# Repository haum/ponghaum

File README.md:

# PongHaum

## Qu'est-ce que c'est ?

Ce dépôt contient les sources de ponghaum, le pong 1D réalisé par le HAUM (http://haum.org/)

## Arduino

### Présentation

Le système utilise 150 leds en bande commandées par la bibliothèque FastLED et deux boutons. Les détails du système est/sera présent sur le site du HAUM.

### Paramétrage

Le paramétrage des pins de l'arduino est réalisé dans le fichier khroma.h avec les constances PINS__*.

Par défaut, les boutons sont reliés aux entrées 2 et 3 et le bandeau de LEDs est relié à la sortie 10.
L'arduino est reliée à une alimentation ATX. Un bouton poussoir POWERSTOP (4) permet de commander l'extinction, une broche POWERCMD (5) est reliée à la commande d'allumage de l'ATX (fil vert) et une broche POWERGOOD (6) permet de détecter l'allumage de l'alimentation.

### Compilation

Lorsque le dépôt est cloné, il faut penser à charger les submodules pour avoir les dépendances permettant de construire le programme pour Arduino.

```
git submodule init
git submodule update
```

Ensuite il est possible d'utiliser le Makefile pour envoyer le programme sur Arduino :

```
make upload
```

Testé avec Arduino 1.0.6

Have fun :)

## Émulateur

### Contôles

Les boutons sont émulés par des touches de calvier :

 - Flèche Gauche ou touche Q sur clavier AZERTY = bouton 1
 - Flèche Droite ou touche D sur clavier AZERTY = bouton 2

Une touche permet aussi de quitter l'émulateur :

 - Échap = Quitter l'émulateur

Les leds sont émulés par des pixels dans une fenêtre.

Les caractères envoyés sur la liaison série sont redirigés vers la sortie standard du programme.

### Raison d'être

Les sources contiennent un émulateur pour le développement et tests sur PC.

Celui-ci permet d'essayer différents programmes sans avoir accès au système électronique, en cours de construction lors de la création du dépôt.
Il faut néanmoins garder en tête que la cible principale est un microcontrôleur 8 bits avec assez peu de mémoire vive.

### Compilation

Le Makefile permet de construire l'émulateur PC (bibliothèque SDL2 nécessaire) :

```
make pc
```

Les dépendances sont seulement pthread et SDL2.

Attention, la variable d'environnement ARDUINO_DIR doit être non nulle (même si elle n'est pas rellement utilisée dans ce cas)

## Licence

Le projet est fourni sous licence MIT.

C'est une licence libre qui vous permet par exemple :
 - de le copier,
 - de l'étudier,
 - de l'adapter à vos besoins,
 - de le redistribuer

Nous vous encourageons vivement à forker et partager !

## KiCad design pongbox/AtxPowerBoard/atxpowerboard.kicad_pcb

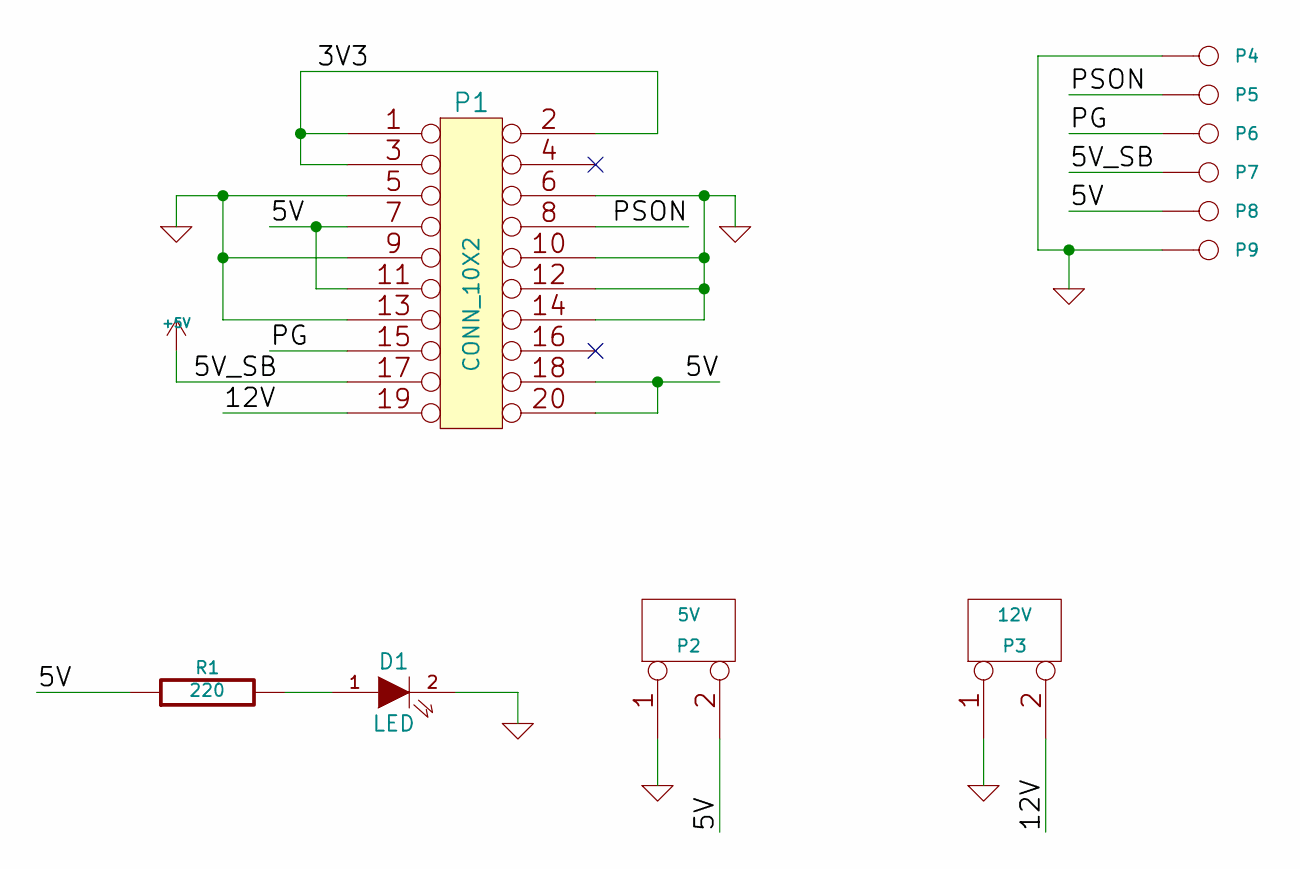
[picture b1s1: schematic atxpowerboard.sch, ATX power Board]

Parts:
D1: LED; LED-5MM
P1: CONN_10X2; ATX20
P2: 5V; bornier2
P3: 12V; bornier2
P4, P5, P6, P7, P8, P9: CONN_1; Pin_Header_Straight_1x01
R1: 220; Resistor_Horizontal_RM10mm

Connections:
+5V: P1.17, P7.1
/3V3: P1.1, P1.2, P1.3
/5V: P1.7, P1.11, P1.18, P1.20, P2.2 (PM), P8.1, R1.1
/12V: P1.19, P3.2 (PM)
/PG: P1.15, P6.1
/PSON: P1.8, P5.1
GND: D1.2 (K), P1.5, P1.6, P1.9, P1.10, P1.12, P1.13, P1.14, P2.1, P3.1, P4.1, P9.1
unnamed: D1.1 (A), R1.2

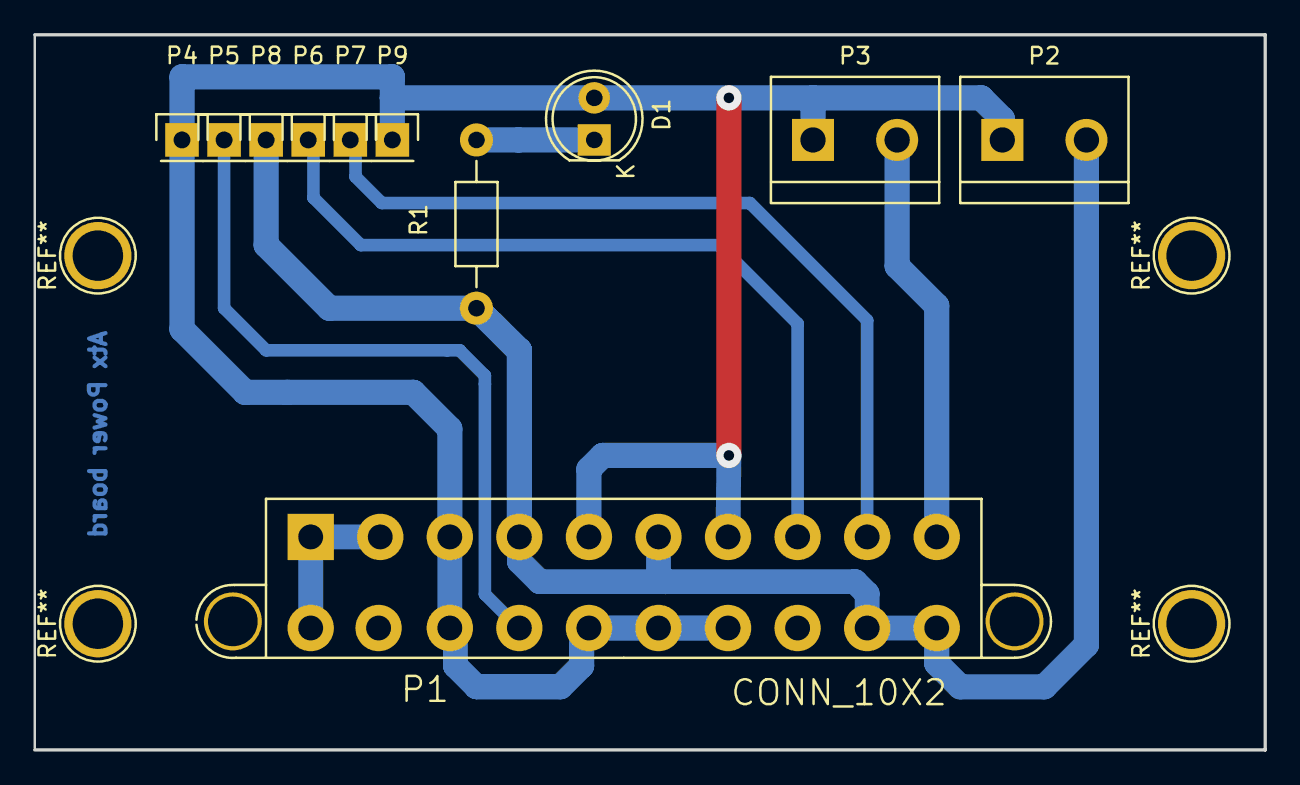
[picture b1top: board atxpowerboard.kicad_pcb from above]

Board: 2 copper layers, 74.3 x 43.2 mm, 11 parts (0 on the bottom side), 8 nets.

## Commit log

2014-08-02 Start project
2014-08-02 Add gitignore rules
2014-08-02 Add HmiManager to interface real world
2014-08-02 Create emulator
2014-08-02 Add GameManager class
2014-08-02 Add dummy Makefile
2014-08-02 Change coordinate system to be symetric
2014-08-02 Add Sprite class
2014-08-02 Add BallSprite
2014-08-02 Add screen skeleton with dummy example
2014-08-02 Add animator
2014-08-02 Use linear animator in WaitPlayers screen
2014-08-02 Add a queue to ball
2014-08-02 Add flickers animations to ball
2014-08-02 Add Animator running info
2014-08-02 Add knee to linear animator
2014-08-02 Add pads sprite
2014-08-02 Finish WaitPlayersScreen and prepare PlayingScreen
2014-08-02 Add ability to send numbers to log
2014-08-02 Add basic gameplay and prepare scrore screen
2014-08-02 Change shiny color of the ball
2014-08-02 Change some speed constants
2014-08-02 Add score screen
2014-08-02 Better game restart
2014-08-02 Add slight improvement to ball queue animation
2014-08-02 Changes in window sizing
2014-08-03 Add licence
2014-08-03 Split HmiManager files
2014-08-03 Add buttons click kinds
2014-08-03 Add TestHardwareScreen + some visual cosmetics
2014-08-03 Correct animator : should stop when not started !
2014-08-03 Add some other visual cosmetics
2014-08-09 Add Q and D keys to emulate buttons
2014-08-09 Small patch which seems to solve score bug... WTF
2014-08-19 Link to Arduino
2014-08-20 Change Makefile.pc to match new file organization
2014-08-20 Remove Makefile soft link (should not be commited)
2014-08-20 Better Arduino makefile with submodules
2014-08-20 Ajout procédure de compilation Arduino
2014-08-20 Cleanup HMI arduino code
2014-08-20 mise a jour du README avec les instructions pour Arduino
2014-08-20 correction pb sur le Fichier README
2014-08-20 Revert "correction pb sur le Fichier README"
    This reverts commit 20cd19ef46f8417ed6204e9a0390f5fde7f0c00f.
2014-08-20 fin de ma galere de merge ....
2014-08-21 Déplacer la configuration des broches Arduino vers le Makefile
    Closes #1
2014-08-21 Mise à jour du README avec la nouvelle procédure de configuration des broches d'Arduino
2014-08-26 Ajout de broches pour la commande de l'alimentation ATX
2014-08-26 Début de l'ajout de l'écran POWEROFF
2014-08-26 Ajout des commandes ON/OFF de l'alim
2014-08-26 Gameplay: celui qui gagne relance la balle
2014-08-26 Changement du ACK sur le tableau de scores
2014-08-26 Changement des constantes de click
2014-08-26 Remplacer des événements pressed par des touched
2014-08-26 Passage des durées des animateurs en float
2014-08-26 Ajout d'une extinction automatique
2014-09-01 Retour à l'écran d'attente si aucune action en 1 minute
2014-09-01 Allongement de l'animation d'attente
2014-09-01 Luminosité 50%
2014-09-01 Retirer l'animation flicker non visible sur la balle
2014-09-01 Vitesse de départ davantage réduite pour les enfants
2014-09-01 Pour gagner, il faut pousser le score de l'autre
    Le nombre de points maxi a été réduit
2014-09-01 Faire démarrer la partie à 2 - 2
2014-09-01 Réduire le délai d'augmentation de la vitesse
2014-09-01 Dernières modifs de Mathieu
2014-09-02 Arc-en-ciel pour Jérôme !
2014-09-03 fichiers d'usinage du boitier et stl boutons
2014-09-04 ajout deuxieme version bouton + readme
2014-09-17 modele de pieds pour la 1DPongBox
2014-09-17 netoyage des fichiers de backup
2015-01-13 game: increase initial speed
2015-01-13 game: fix CONQUER bugs
    Points were added to the wrong player
2015-06-09 Ajout de modeles aux formats STL et IGS de manettes adaptées aux nouveaux boutons de 30mm.
2015-06-30 Correction des dimensions des manettes pour l'impression
2015-07-07 hmi: change click timings
2015-09-13 Use PolychrHAUM library
2015-09-18 Add missing Makefile
2015-09-18 Update PolychrHAUM library
2015-09-18 Add precisions about SDL2 library requierement for pc version
2015-09-22 Ajout fichiers carte AtxPowerBoard
2015-09-22 ajust dimentions de la carte
2015-09-27 Keep track of old score before modification
2015-09-27 Display a red led at the end of led strip that has triggered a double press
2015-09-27 Score: Animate only the last won point and implement conquer-mode push animation
2015-09-27 score: display a separator between score units
2015-09-27 wait_players : use true/false or CPP boolean
2015-09-27 Added attack, once a game, you can make the ball invisible by double clicking
2015-09-27 Revert "Added attack, once a game, you can make the ball invisible by double clicking"
    Boni must be developped and stored in branches
    This reverts commit 1709d636417d9892c1e60f300f2c1d04ec8d6c1e.
2016-03-15 add fritzing schematic
2016-03-15 fritzing schematic update
2016-03-26 Ajout de l'affichage de la version sur le port serie (pong) ou dans la console (emulateur)
2016-03-26 Ajout de l'affichage de la version
2016-03-27 Ajout de couleur de balle différente en mode démo
2016-03-27 Modification de la couleur de la balle en fin de course
2016-03-28 Correction bug couleur sur la version PC
2017-04-30 add marker to signal where is the end of led band
2018-01-12 Link schematic image in README.md
2018-08-02 Prepare playing4x_screen
2018-08-07 Add random direction
2018-08-07 Remove ugly version macro
2018-08-07 Remove 1.0.0-MASTER and add 1.0.0-PLAYER4X-Alpha
2018-08-07 Add a message about the 4 players game mode
2018-08-14 Add makefile target to launch two connected ponhaum on PC
2018-08-14 add 4 players initialization test
2018-08-14 Add communication skeletton
2018-08-14 update arduino-mk submodule
2018-08-14 add configuration of our two pongs in Makefile
2018-08-21 Auto start playing4x screen on the other axis
2018-08-21 Remove mode conquer for the moment
2018-08-21 Set 'autopong' mode
2018-08-21 Add mode for switch queue of the ball from the master
2018-08-25 Add implementation of different sending modes
    The function make_msg() update a 4 char array. This char array **must** be
    declared **before** use the function.
2020-08-06 Revert "Ajout de l'affichage de la version sur le port serie (pong) ou dans la console (emulateur)"
    This reverts commit db92a7815cb98b42d3308a070497de9f49f95953.
    Useless and not in sync with actual version
2020-08-30 Hack after button1 is broken
2020-08-30 Second version of the hack
2020-08-30 Add an indicator when the button stays clicked
